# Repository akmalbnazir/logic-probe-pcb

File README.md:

# 🧠 Logic Probe Tool (USB-Powered)

A simple but powerful **USB-powered logic probe** built in **KiCad**. This compact tool visually detects whether a digital signal is **HIGH** or **LOW** using two LEDs — great for debugging microcontroller pins, communication lines, or basic digital logic gates.

---

## 🔌 Features

- ✅ **USB-C powered** — no external batteries
- 🔴 **Red LED** lights when signal is LOW
- 🟢 **Green LED** lights when signal is HIGH
- 🔁 Built with a **74HC14 Schmitt Trigger inverter**
- 🔥 Protected by a **PTC resettable fuse** and **Schottky diode**
- 🧪 **Voltage divider** ensures safe signal detection
- 🛡️ Ground-referenced probe tip with pull-down resistor
- 💡 Fits on a small 2-layer PCB, ideal for hand-soldering

---

## 📐 Schematic Overview

The probe input passes through two inverters on a 74HC14 IC:
- One output drives the **RED LED** (LOW indicator)
- The other drives the **GREEN LED** (HIGH indicator)

Power comes from USB-C and is protected with:
- A **Schottky diode** for reverse polarity
- A **PTC fuse** for overcurrent protection
- **Bypass capacitors** for stable voltage

---

## 🧰 BOM (Bill of Materials)

| Component     | Value/Part             |
|---------------|------------------------|
| USB Connector | USB_C_Receptacle_USB2.0_16P |
| U1            | 74HC14 Schmitt Inverter |
| F1            | Polyfuse 500mA         |
| D1            | Schottky Diode (e.g., SS14) |
| R1            | 10kΩ pull-down         |
| R2, R3        | 220Ω LED current limit |
| D2            | Red LED                |
| D3            | Green LED              |
| C1, C2        | 0.1 µF & 10 µF ceramic capacitors |
| J2            | Probe input pin header |
| GND Pad       | Ground contact pad     |

---

## 🧠 Usage

1. Plug the logic probe into a USB-C power source.
2. Touch the **probe pin** to any digital signal line (3.3V or 5V logic).
3. Observe:
   - 🔴 Red LED = LOW (0V)
   - 🟢 Green LED = HIGH (3.3V/5V)
4. The pull-down resistor ensures stable readings even on floating lines.

---

## 📸 Preview

---

## 🛠 Files Included

- `logic-probe.kicad_pro` — project file
- `logic-probe.kicad_sch` — schematic
- `logic-probe.kicad_pcb` — PCB layout
- `gerbers/` — ready-to-manufacture fabrication files
- `README.md` — this documentation

---

## 📜 License

MIT License — free to use, modify, and distribute. Give credit if you build on this work.

---

## 👨‍💻 Author

Designed by Akmal Nazir – May 2025  
KiCad-powered, beginner-friendly, proudly hand-soldered.

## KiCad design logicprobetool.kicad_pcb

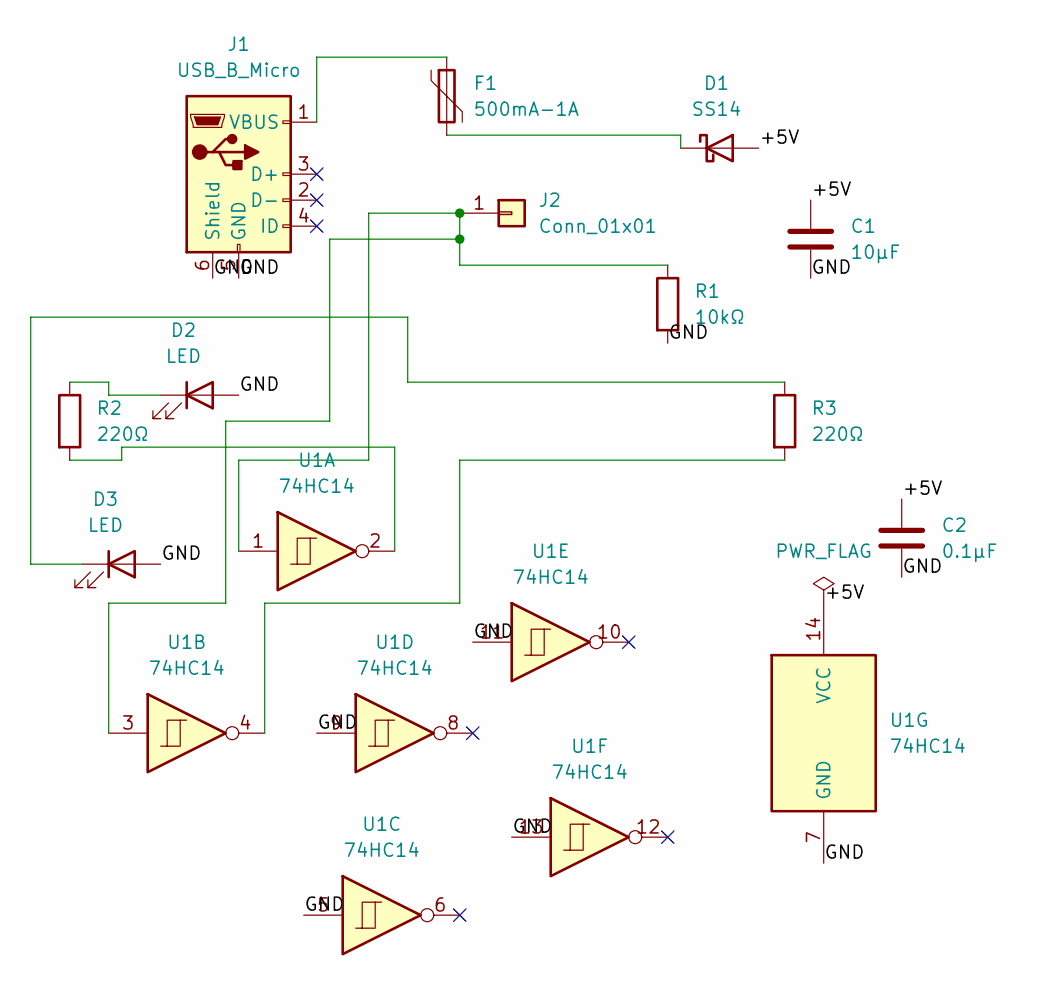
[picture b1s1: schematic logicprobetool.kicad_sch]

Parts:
C1: 10µF; C_0603_1608Metric
C2: 0.1µF; C_0603_1608Metric
D1: SS14; D_SMA
D2, D3: LED; LED_0603_1608Metric
F1: 500mA-1A; Fuse_1206_3216Metric
J1: USB_B_Micro; USB_Micro-B_Molex-105017-0001
J2: Conn_01x01; PinHeader_1x01_P2.54mm_Vertical
R1: 10kΩ; R_0603_1608Metric
R2, R3: 220Ω; R_0603_1608Metric
U1: 74HC14; SOIC-14_3.9x8.7mm_P1.27mm

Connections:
/+5V: C1.1, C2.1, D1.2 (A), U1.14 (VCC)
/GND: C1.2, C2.2, D2.2 (A), D3.2 (A), J1.5 (GND), J1.6 (Shield), R1.2, U1.5, U1.7 (GND), U1.9, U1.11, U1.13
unnamed: D1.1 (K), F1.2
unnamed: D2.1 (K), R2.1
unnamed: D3.1 (K), R3.1
unnamed: F1.1, J1.1 (VBUS)
unnamed: J2.1, R1.1, U1.1, U1.3
unnamed: R2.2, U1.2
unnamed: R3.2, U1.4

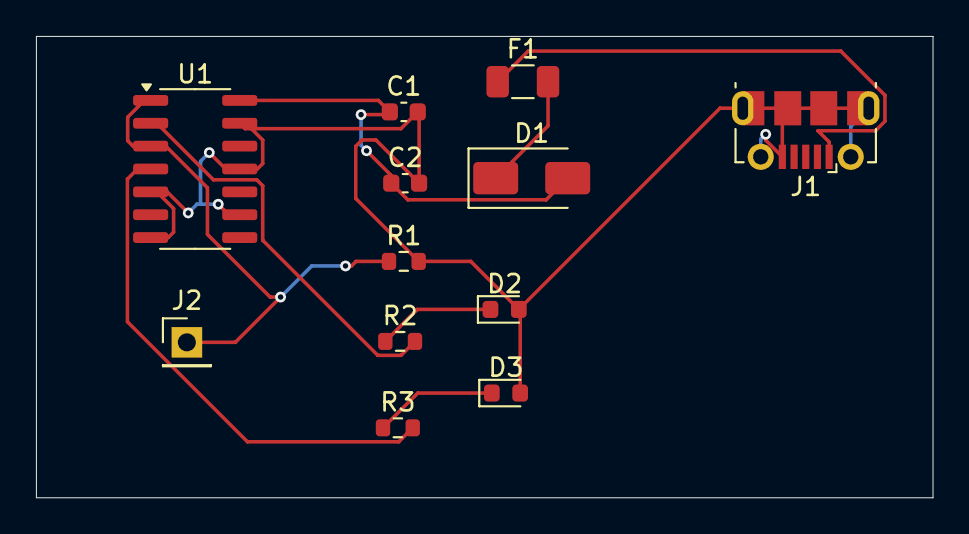
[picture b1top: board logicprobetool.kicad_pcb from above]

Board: 2 copper layers, 49.8 x 25.6 mm, 12 parts (0 on the bottom side), 9 nets.

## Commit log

2025-05-11 Initial commit - Logic Probe Tool in KiCad
